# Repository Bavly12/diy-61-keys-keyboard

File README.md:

this is the switches from Amazon https://a.co/d/agXA1SN
and this is the keycaps https://amzn.eu/d/1OEAuBD at this case you will need the 61 keycaps
and this is the space stapleizer https://amzn.eu/d/1TKf2iF
and this is the micro controller https://amzn.eu/d/1xMigXm
and the jumper wires https://amzn.eu/d/buaqOeA

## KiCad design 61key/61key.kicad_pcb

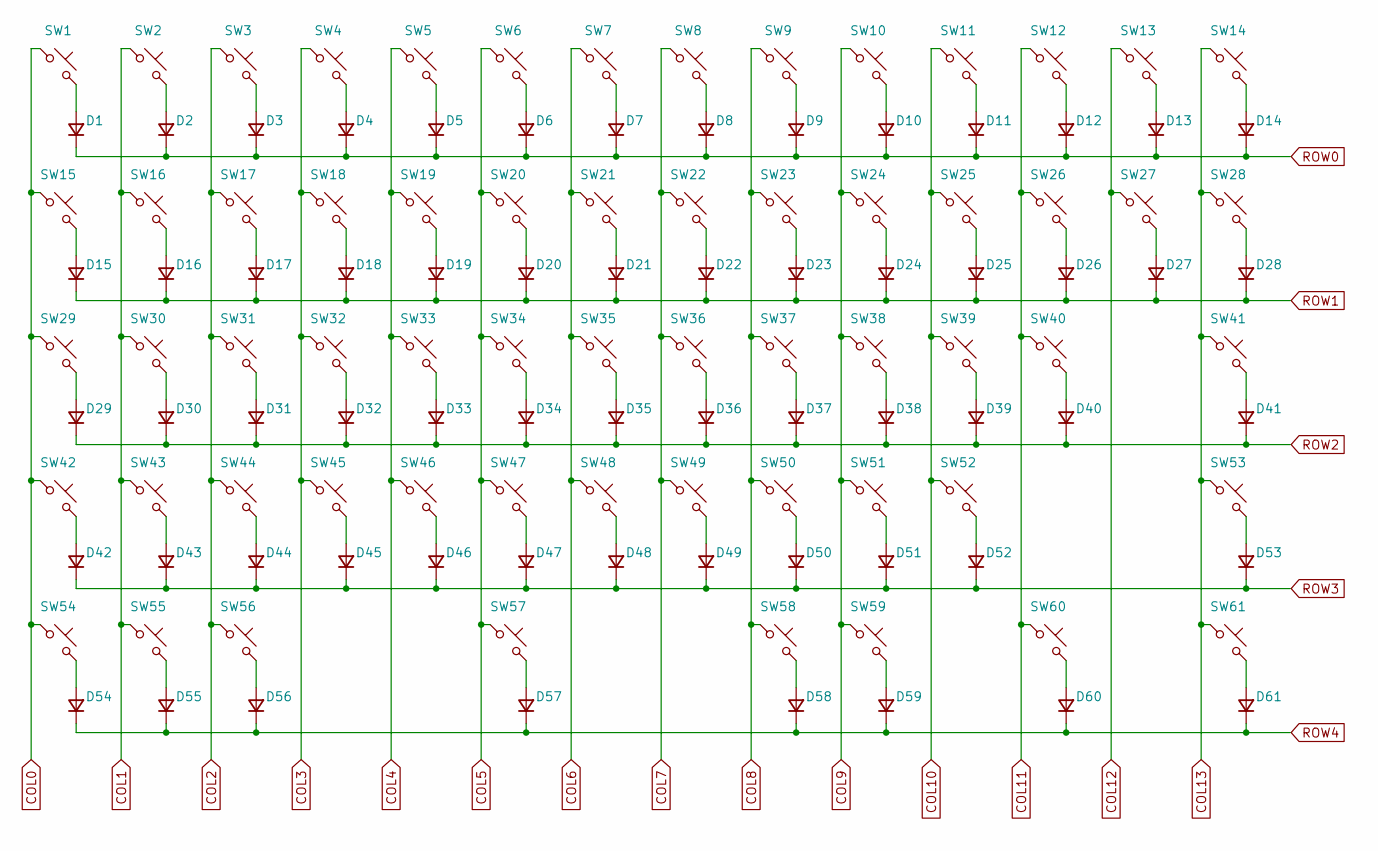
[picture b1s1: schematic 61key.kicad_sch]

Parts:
D1, D2, D3, D4, D5, D6, D7, D8, D9, D10, D11, D12, D13, D14, D15, D16, D17, D18, D19, D20, D21, D22, D23, D24, D25, D26, D27, D28, D29, D30, D31, D32, D33, D34, D35, D36, D37, D38, D39, D40, D41, D42, D43, D44, D45, D46, D47, D48, D49, D50, D51, D52, D53, D54, D55, D56, D57, D58, D59, D60, D61: D; D_SOD-123F
SW1, SW2, SW3, SW4, SW5, SW6, SW7, SW8, SW9, SW10, SW11, SW12, SW13, SW14, SW15, SW16, SW17, SW18, SW19, SW20, SW21, SW22, SW23, SW24, SW25, SW26, SW27, SW28, SW29, SW30, SW31, SW32, SW33, SW34, SW35, SW36, SW37, SW38, SW39, SW40, SW41, SW42, SW43, SW44, SW45, SW46, SW47, SW48, SW49, SW50, SW51, SW52, SW53, SW54, SW55, SW56, SW57, SW58, SW59, SW60, SW61: SW_Push; SW_Cherry_MX_PCB_1.00u

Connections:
COL0: SW1.1, SW15.1, SW29.1, SW42.1, SW54.1
COL1: SW2.1, SW16.1, SW30.1, SW43.1, SW55.1
COL2: SW3.1, SW17.1, SW31.1, SW44.1, SW56.1
COL3: SW4.1, SW18.1, SW32.1, SW45.1
COL4: SW5.1, SW19.1, SW33.1, SW46.1
COL5: SW6.1, SW20.1, SW34.1, SW47.1, SW57.1
COL6: SW7.1, SW21.1, SW35.1, SW48.1
COL7: SW8.1, SW22.1, SW36.1, SW49.1
COL8: SW9.1, SW23.1, SW37.1, SW50.1, SW58.1
COL9: SW10.1, SW24.1, SW38.1, SW51.1, SW59.1
COL10: SW11.1, SW25.1, SW39.1, SW52.1
COL11: SW12.1, SW26.1, SW40.1, SW60.1
COL12: SW13.1, SW27.1
COL13: SW14.1, SW28.1, SW41.1, SW53.1, SW61.1
unnamed: D1.2 (A), SW1.2
unnamed: D2.2 (A), SW2.2
unnamed: D3.2 (A), SW3.2
unnamed: D4.2 (A), SW4.2
unnamed: D5.2 (A), SW5.2
unnamed: D6.2 (A), SW6.2
unnamed: D7.2 (A), SW7.2
unnamed: D8.2 (A), SW8.2
unnamed: D9.2 (A), SW9.2
unnamed: D10.2 (A), SW10.2
unnamed: D11.2 (A), SW11.2
unnamed: D12.2 (A), SW12.2
unnamed: D13.2 (A), SW13.2
unnamed: D14.2 (A), SW14.2
unnamed: D15.2 (A), SW15.2
unnamed: D16.2 (A), SW16.2
unnamed: D17.2 (A), SW17.2
unnamed: D18.2 (A), SW18.2
unnamed: D19.2 (A), SW19.2
unnamed: D20.2 (A), SW20.2
unnamed: D21.2 (A), SW21.2
unnamed: D22.2 (A), SW22.2
unnamed: D23.2 (A), SW23.2
unnamed: D24.2 (A), SW24.2
unnamed: D25.2 (A), SW25.2
unnamed: D26.2 (A), SW26.2
unnamed: D27.2 (A), SW27.2
unnamed: D28.2 (A), SW28.2
unnamed: D29.2 (A), SW29.2
unnamed: D30.2 (A), SW30.2
unnamed: D31.2 (A), SW31.2
unnamed: D32.2 (A), SW32.2
unnamed: D33.2 (A), SW33.2
unnamed: D34.2 (A), SW34.2
unnamed: D35.2 (A), SW35.2
unnamed: D36.2 (A), SW36.2
unnamed: D37.2 (A), SW37.2
unnamed: D38.2 (A), SW38.2
unnamed: D39.2 (A), SW39.2
unnamed: D40.2 (A), SW40.2
unnamed: D41.2 (A), SW41.2
unnamed: D42.2 (A), SW42.2
unnamed: D43.2 (A), SW43.2
unnamed: D44.2 (A), SW44.2
unnamed: D45.2 (A), SW45.2
unnamed: D46.2 (A), SW46.2
unnamed: D47.2 (A), SW47.2
unnamed: D48.2 (A), SW48.2
unnamed: D49.2 (A), SW49.2
unnamed: D50.2 (A), SW50.2
unnamed: D51.2 (A), SW51.2
unnamed: D52.2 (A), SW52.2
unnamed: D53.2 (A), SW53.2
unnamed: D54.2 (A), SW54.2
unnamed: D55.2 (A), SW55.2
unnamed: D56.2 (A), SW56.2
unnamed: D57.2 (A), SW57.2
unnamed: D58.2 (A), SW58.2
unnamed: D59.2 (A), SW59.2
unnamed: D60.2 (A), SW60.2
unnamed: D61.2 (A), SW61.2
ROW0: D1.1 (K), D2.1 (K), D3.1 (K), D4.1 (K), D5.1 (K), D6.1 (K), D7.1 (K), D8.1 (K), D9.1 (K), D10.1 (K), D11.1 (K), D12.1 (K), D13.1 (K), D14.1 (K)
ROW1: D15.1 (K), D16.1 (K), D17.1 (K), D18.1 (K), D19.1 (K), D20.1 (K), D21.1 (K), D22.1 (K), D23.1 (K), D24.1 (K), D25.1 (K), D26.1 (K), D27.1 (K), D28.1 (K)
ROW2: D29.1 (K), D30.1 (K), D31.1 (K), D32.1 (K), D33.1 (K), D34.1 (K), D35.1 (K), D36.1 (K), D37.1 (K), D38.1 (K), D39.1 (K), D40.1 (K), D41.1 (K)
ROW3: D42.1 (K), D43.1 (K), D44.1 (K), D45.1 (K), D46.1 (K), D47.1 (K), D48.1 (K), D49.1 (K), D50.1 (K), D51.1 (K), D52.1 (K), D53.1 (K)
ROW4: D54.1 (K), D55.1 (K), D56.1 (K), D57.1 (K), D58.1 (K), D59.1 (K), D60.1 (K), D61.1 (K)

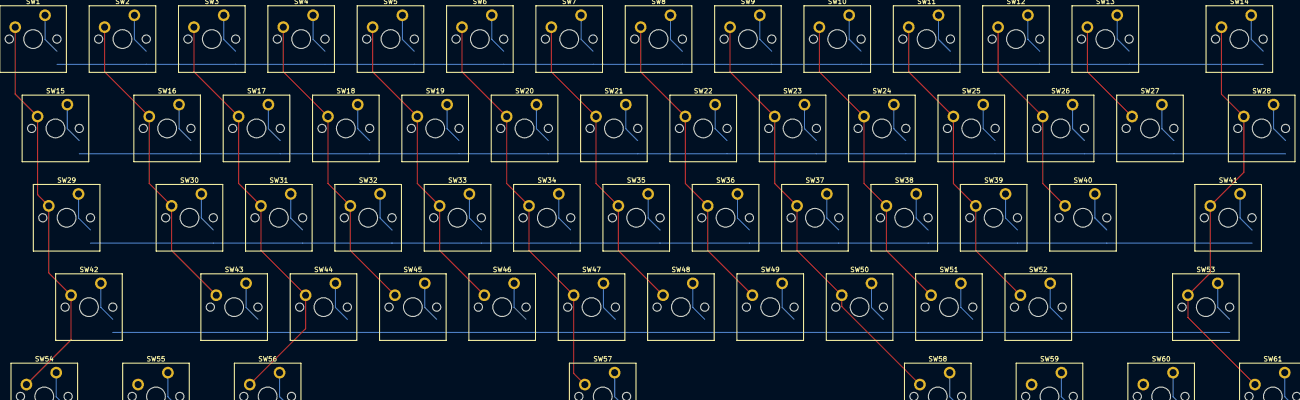
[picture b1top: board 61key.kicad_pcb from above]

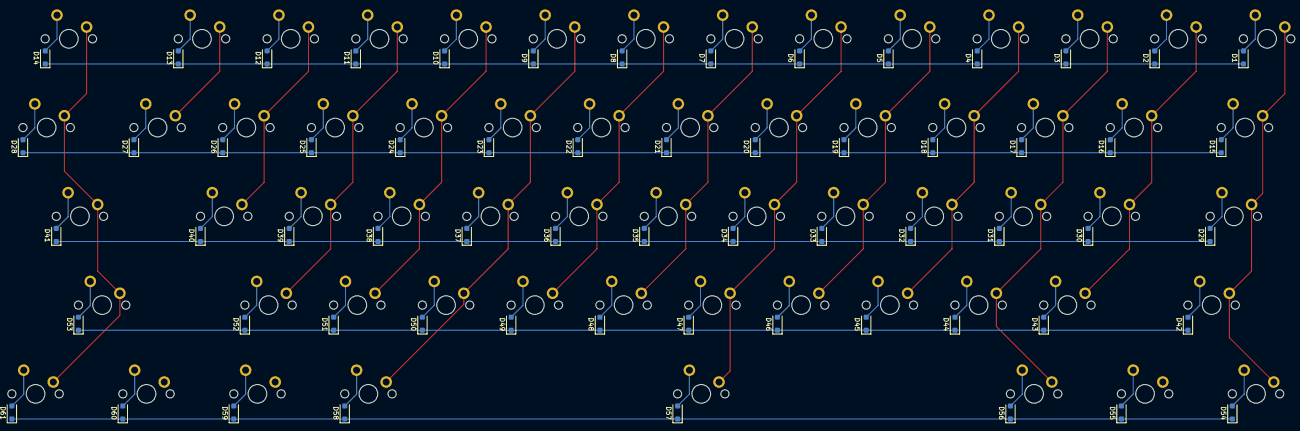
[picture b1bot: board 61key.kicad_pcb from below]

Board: 2 copper layers, 122 parts (61 on the bottom side), 80 nets.
